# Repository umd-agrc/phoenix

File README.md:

# Rotocrawler
This project’s aim is to develop a autonomous, self-tuning navigation system for a robotic platform using an artificial neural network. The robotic platform being designed for this project has the functionality of a micro-aerial vehicle (i.e., MAV or “drone”) and a quadruped crawling robot– meaning that it can both walk and fly depending on the environmental context and its specified goal. The autonomous, self-tuning navigation system uses an optimized schedule for flight and crawl pairing, given a context and goal. The choice of an autonomous navigator alleviates the operator from having to consider or maintain awareness of a large number of sensor or heuristic vehicle state.
## Dependencies
* roscpp
* rospy
* std_msgs
* sensor_msgs
* cv_bridge
* image_transport

## Included in build
* OpenCV

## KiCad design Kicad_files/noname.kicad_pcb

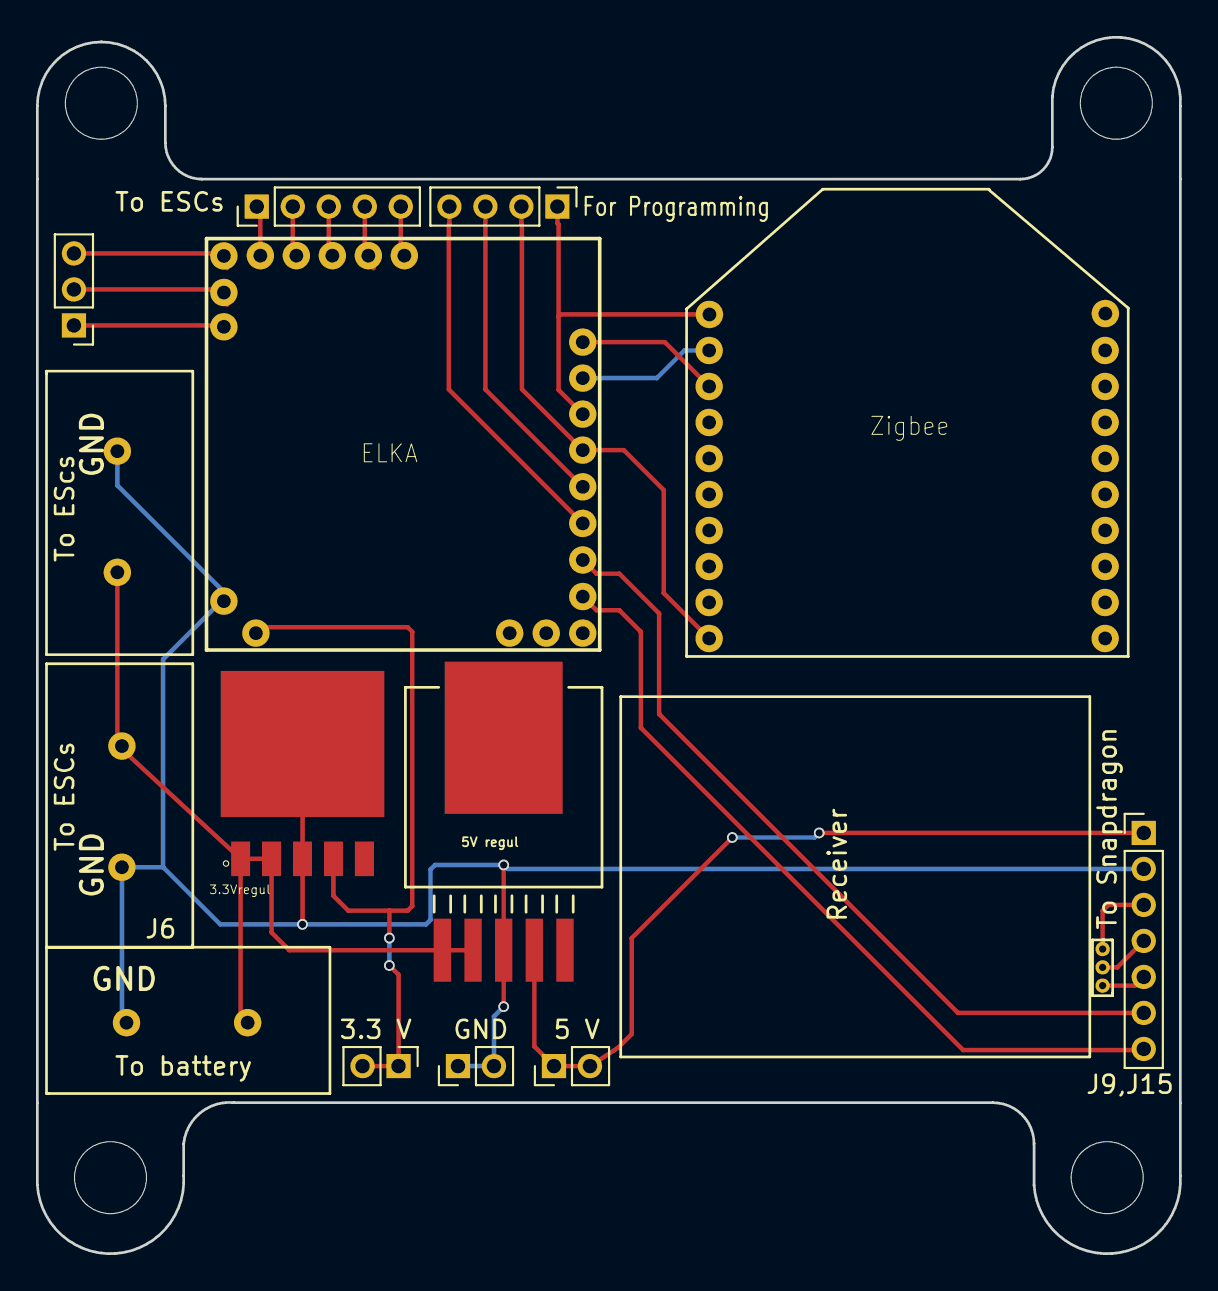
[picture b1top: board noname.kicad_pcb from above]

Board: 2 copper layers, 63.5 x 67.6 mm, 12 parts (0 on the bottom side), 20 nets.

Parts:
ELKA: ELKA
J1: To battery; XT30
J3: 3.3 V; Pin_Header_Straight_1x02_Pitch2.00mm
J4: GND; Pin_Header_Straight_1x02_Pitch2.00mm
J5: 5 V; Pin_Header_Straight_1x02_Pitch2.00mm
J6: To ESCs; XT30
J9,J15: To Snapdragon; Pin_Header_Straight_1x07_Pitch2.00mm
J16: For Programming; Pin_Header_Straight_1x04_Pitch2.00mm
R1: Receiver; SPMAJST6
To ESCs: Pin_Header_Straight_1x05_Pitch2.00mm
To EScs: To ESCs; XT30
Zigbee: Zigbee; DIP-20

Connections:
unnamed: ELKA.4, To ESCs.1
unnamed: ELKA.5, To ESCs.2
unnamed: ELKA.6, To ESCs.3
unnamed: ELKA.7, To ESCs.4
unnamed: ELKA.8, To ESCs.5
unnamed: ELKA.11, J1.1, J4.1, J4.2, J6.1, J9,J15.2, To EScs.1
unnamed: ELKA.12, J3.1, J3.2
unnamed: ELKA.A, Zigbee.3
unnamed: ELKA.B, Zigbee.2
unnamed: ELKA.C, J16.1, Zigbee.1
unnamed: ELKA.D, J16.2, Zigbee.10
unnamed: ELKA.E, J16.3
unnamed: ELKA.F, J16.4
unnamed: ELKA.G, J9,J15.6
unnamed: ELKA.H, J9,J15.7
unnamed: J1.2, J6.2, To EScs.2
unnamed: J5.1, J5.2, J9,J15.1
unnamed: J9,J15.3, R1.1
unnamed: J9,J15.4, R1.2
unnamed: J9,J15.5, R1.3

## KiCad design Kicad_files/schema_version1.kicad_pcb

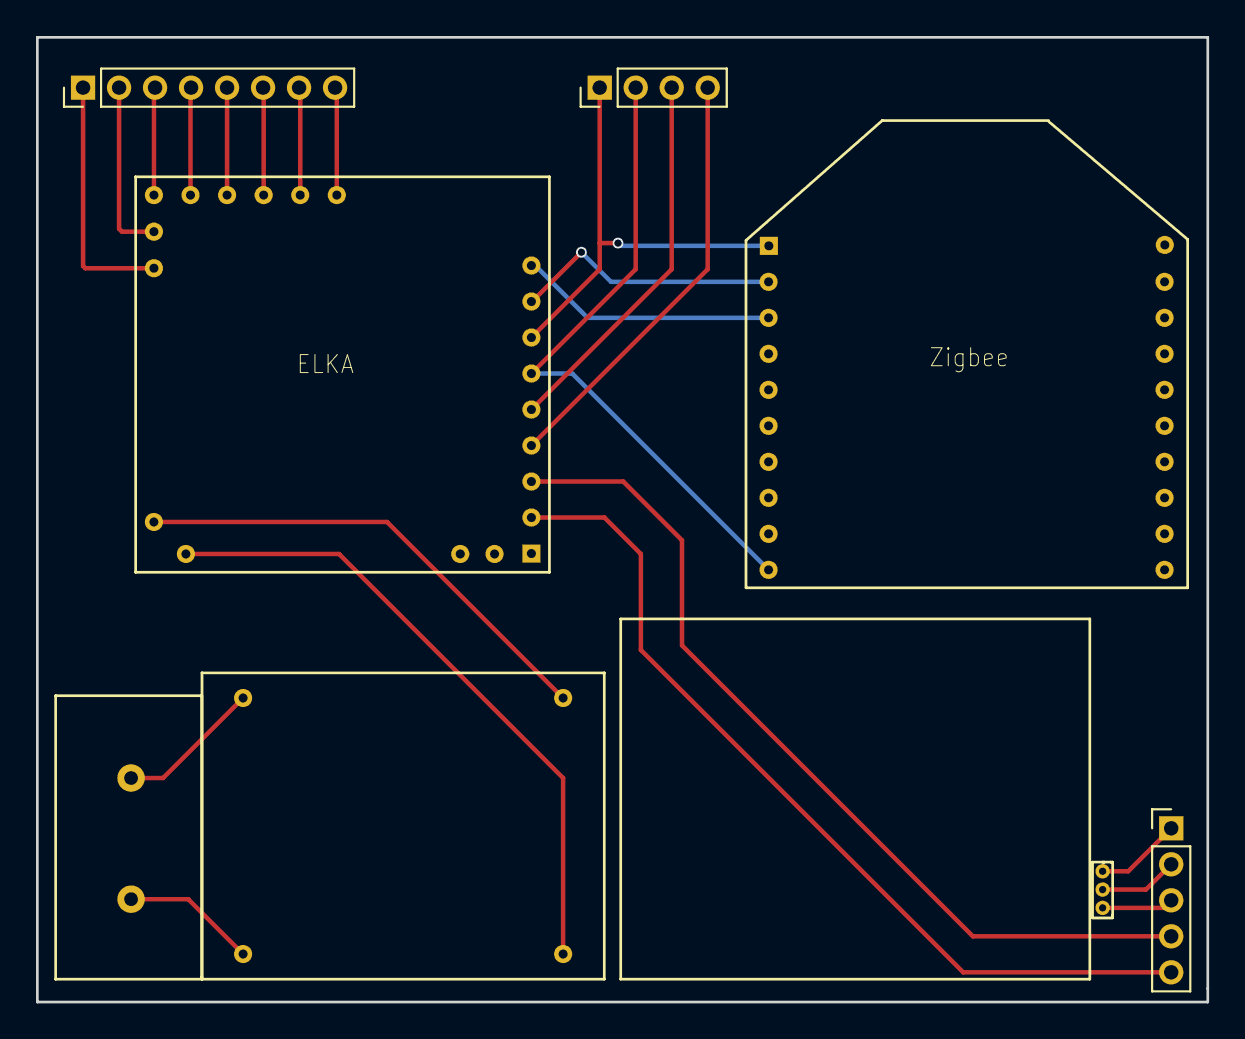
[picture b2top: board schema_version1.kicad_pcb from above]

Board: 2 copper layers, 65.0 x 53.6 mm, 8 parts (0 on the bottom side), 23 nets.

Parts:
ELKA: ELKA
J1: To battery; XT30
J2: To ESCs; Pin_Header_Straight_1x08_Pitch2.00mm
J9: To Snapdragon; Pin_Header_Straight_1x05_Pitch2.00mm
J16: For Programming; Pin_Header_Straight_1x04_Pitch2.00mm
R1: Receiver; SPMAJST6
V1: VRM
Zigbee: Zigbee; DIP-20

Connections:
unnamed: ELKA.1, J2.1
unnamed: ELKA.2, J2.2
unnamed: ELKA.3, J2.3
unnamed: ELKA.4, J2.4
unnamed: ELKA.5, J2.5
unnamed: ELKA.6, J2.6
unnamed: ELKA.7, J2.7
unnamed: ELKA.8, J2.8
unnamed: ELKA.11, V1.4
unnamed: ELKA.12, V1.3
unnamed: ELKA.A, Zigbee.3
unnamed: ELKA.B, Zigbee.2
unnamed: ELKA.C, J16.1, Zigbee.1
unnamed: ELKA.D, J16.2, Zigbee.10
unnamed: ELKA.E, J16.3
unnamed: ELKA.F, J16.4
unnamed: ELKA.G, J9.4
unnamed: ELKA.H, J9.5
unnamed: J1.1, V1.1
unnamed: J1.2, V1.2
unnamed: J9.1, R1.1
unnamed: J9.2, R1.2
unnamed: J9.3, R1.3

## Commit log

2018-06-05 adding directory structure
2018-06-05 with new files
2018-06-05 formatting readme
2018-06-08 First_meedting_draft
2018-07-05 Updated to Reflect project branch
    Hey guys,
    I'm using this branch of phoenix as a repo for my Rotocrawler code. It seems I can't make my own repo under AGRC, so I'm piggy-backing off you. I'll move it if I get my own repo in the future. Thanks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
2018-07-05 CMakeLists.txt
2018-07-05 package.xml
2018-07-05 Put it in it's directory
    Now it is in the correct directory for ROS
2018-07-05 Rename CMakeLists.txt to rotocopter/CMakeLists.txt
2018-07-05 Rename rotocopter/CMakeLists.txt to rotocrawler/CMakeLists.txt
2018-07-05 Rename rotocopter/msg/package.xml to rotocrawler/msg/package.xml
2018-07-05 scripts for image nodes
2018-07-05 Rename rotocrawler/image_publisher.py to rotocrawler/scripts/image_publisher.py
2018-07-05 Rename rotocrawler/image_subscriber.py to rotocrawler/scripts/image_subscriber.py
2018-07-05 Added some dependencies
2018-07-11 now it can launch multiple nodes
2018-07-11 still broken
    needs fixing
2018-07-11 first iteration of launch file
    needs work on remapping topic names
2018-07-11 put it in its directory
2018-07-13 Create snapdragon
2018-07-17 Rename params.yaml to catkin_workspace/params.yaml
2018-07-17 Rename toplevel.cmake to catkin_workspace/toplevel.cmake
2018-07-17 Rename rotocrawler/launch/rotocrawler.launch to catkin_workspace/rotocrawler/launch/rotocrawler.launch
2018-07-17 Rename rotocrawler/msg/package.xml to catkin_workspace/rotocrawler/package.xml
2018-07-17 Rename rotocrawler/scripts/image_publisher.py to catkin_workspace/rotocrawler/scripts/image_publisher.py
2018-07-17 Rename catkin_workspace/rotocrawler/launch/rotocrawler.launch to catkin_workspace/src/rotocrawler/launch/rotocrawler.launch
2018-07-17 Rename catkin_workspace/rotocrawler/package.xml to catkin_workspace/src/rotocrawler/package.xml
2018-07-17 Rename catkin_workspace/rotocrawler/scripts/image_publisher.py to catkin_workspace/src/rotocrawler/scripts/image_publisher.py
2018-07-17 Rename rotocrawler/scripts/image_subscriber.py to catkin_workspace/src/rotocrawler/scripts/image_subscriber.py
2018-07-17 Rename rotocrawler/CMakeLists.txt to catkin_workspace/src/rotocrawler/CMakeLists.txt
2018-07-17 Rename catkin_workspace/.built_by to catkin_workspace/build/.built_by
2018-07-17 Rename catkin_workspace/CMakeCache.txt to catkin_workspace/build/CMakeCache.txt
2018-07-17 Rename catkin_workspace/CTestTestfile.cmake to catkin_workspace/build/CTestTestfile.cmake
2018-07-17 Rename catkin_workspace/Makefile to catkin_workspace/build/Makefile
2018-07-17 Rename catkin_workspace/catkin_make.cache to catkin_workspace/build/catkin_make.cache
2018-07-17 Rename catkin_workspace/cmake_install.cmake to catkin_workspace/build/cmake_install.cmake
2018-07-17 Rename catkin_workspace/install_manifest.txt to catkin_workspace/build/install_manifest.txt
2018-07-17 Rename catkin_workspace/package.cmake to catkin_workspace/build/catkin/catkin_generated/version/package.cmake
2018-07-17 Rename catkin_workspace/build/env_cached.sh to catkin_workspace/build/catkin_generated/env_cached.sh
2018-07-17 Rename catkin_workspace/build/generate_cached_setup.py to catkin_workspace/build/catkin_generated/generate_cached_setup.py
2018-07-17 Rename catkin_workspace/build/catkin_generated/.rosinstall to catkin_workspace/build/catkin_generated/installspace/.rosinstall
2018-07-17 Rename catkin_workspace/build/catkin_generated/_setup_util.py.stamp to catkin_workspace/build/catkin_generated/stamps/Project/_setup_util.py.stamp
2018-07-17 Rename catkin_workspace/.built_by to catkin_workspace/devel/.built_by
2018-07-19 Don't know why this wasn't commited before
2018-07-19 The Full filesystem for rotocrawler
2018-07-19 this should fix it
2018-07-19 Setup incorrectly. Shouldn't have included entire workspace. Now with just the project folder.
2018-07-19 Okay, this lets us just download this branch under "rotocrawler" and call it good.
2018-07-20 now with approximate time sync and stereo launch files.
2018-07-20 modified: launch/rotocrawler.launch modified: src/image_subscriber.cpp
2018-07-27 modified: launch/rotocrawler.launch
2018-09-04 pcb_version2
2018-09-05 Revert "Merge branch 'master' of https://github.com/umd-agrc/phoenix"
    This reverts commit 33a074875c52529c6a6d7c747bda69b1853c0723, reversing
    changes made to 37208d75ca652f1e076608a5303df500f6241095.
    Reorganizing Kicad files into a new folder
2018-09-05 shifted_kicad_files_into_kicad_files_folder
2018-09-05 placed_kicad_files_into_kicad_files_folder_previous_commit_not_proper
2018-09-05 merged_with_repo_files
2018-09-27 modified: package.xml
2018-09-27 modified: CMakeLists.txt modified: package.xml
